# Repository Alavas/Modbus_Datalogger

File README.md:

# Modbus_Datalogger

Web based data logger.

This device can communicate with any of the Grundfos E-Products through a ModBus interface. Currently it the programming is optimized to work with the Magna3 product line. The Parallax Propeller receives the ModBus data over RS485 and then does the decoding and unit conversion of the pump data. The Electric Imp (SD card shape) polls the Propeller for the new data and then adds its own data. The Electric Imp currently has 3 external thermistors as well as its on board light sensor. This data is packaged on the device and send on to the Electric Imp agent(https://electricimp.com/docs/api/agent/). The Imp agent then breaks up the data and sends the requested data to the Phant(http://phant.io/about/) data server. The server exists currently on a Amazon Web Services EC2 Micro Instance Linux server. In order to view the data a web page interface is used. This web page uses Google Charts to display data from the Phant server. Additional static information is displayed at the bottom of the web page, this information is grabbed from the Electric Imp agent.

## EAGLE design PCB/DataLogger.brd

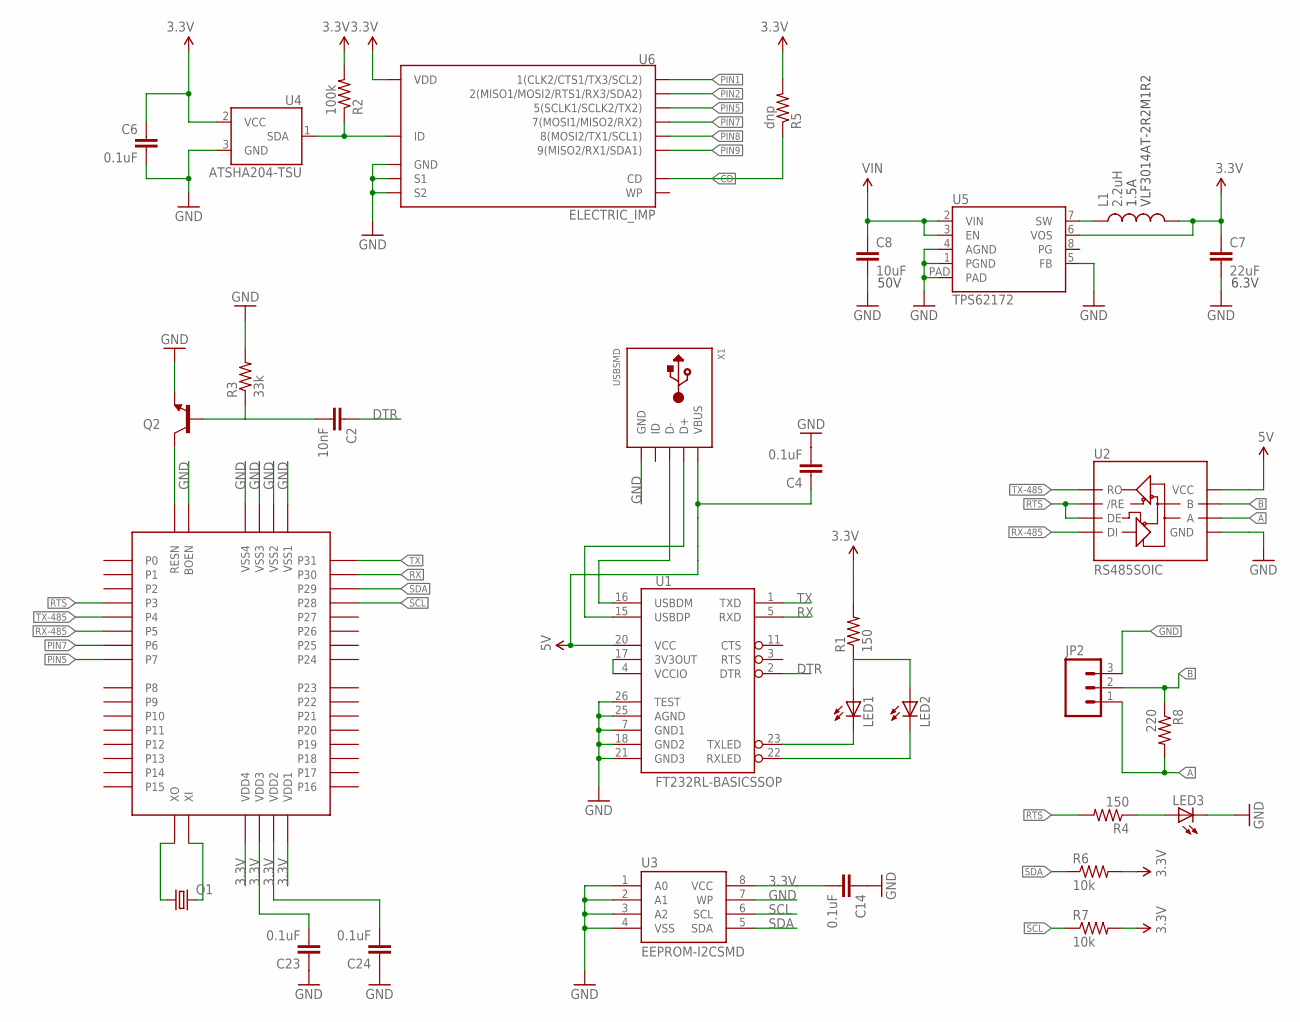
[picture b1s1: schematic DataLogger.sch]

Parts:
C2: 10nF; 0805
C4: 0.1uF; 1210
C6: 0.1uF; 0603-CAP
C7: 22uF; 0805
C8: 10uF; 1210
C14, C23, C24: 0.1uF; 0805
JP2: M03PTH; 1X03
L1: 2.2uH; VLF4012A
LED1, LED2, LED3: LED1206; LED-1206
Q1: CRYSTALSM49; SM49
Q2: TRANSISTOR_NPNSOT23; SOT23
R1, R4: 150; 0805
R2: 100k; 0603-RES
R3: 33k; 0805
R5: dnp; 0603-RES
R6, R7: 10k; 0805
R8: 220; 0805
U1: FT232RL-BASICSSOP; SSOP28DB
U2: RS485SOIC; SO08
U3: EEPROM-I2CSMD; SO08
U4: ATSHA204-TSU; SOT23-3
U5: TPS62172; WSON-8-PAD
U6: ELECTRIC_IMP; SD_1:1
U7: PROPELLERSURFACELQFP; SURFACEMOUNT
X1: USBSMD; USB-MINIB

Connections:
3.3V: C6.1, C7.1, C14.2, C23.2, C24.2, L1.P$2 (2), R1.2, R2.2, R5.2, R6.2, R7.2, U3.8 (VCC), U4.2 (VCC), U5.6 (VOS), U6.4 (VDD), U7.8 (VDD1), U7.18 (VDD2), U7.30 (VDD3), U7.40 (VDD4)
5V: C4.1, C8.1, U1.20 (VCC), U2.8 (VCC), U5.2 (VIN), U5.3 (EN), X1.VBUS
A: JP2.1, R8.2, U2.6 (A)
B: JP2.2, R8.1, U2.7 (B)
CD: R5.1, U6.CD
DTR: C2.1, C2.2, Q2.1 (B), R3.1, U1.2 (DTR)
GND: C4.2, C6.2, C7.2, C8.2, C14.1, C23.1, C24.1, JP2.3, LED3.C, Q2.2 (E), R3.2, U1.7 (GND1), U1.18 (GND2), U1.21 (GND3), U1.25 (AGND), U1.26 (TEST), U2.5 (GND), U3.1 (A0), U3.2 (A1), U3.3 (A2), U3.4 (VSS), U3.7 (WP), U4.3 (GND), U5.1 (PGND), U5.4 (AGND), U5.5 (FB), U5.PAD, U6.3 (GND), U6.SH@1 (S1), U6.SH@2 (S2), U7.5 (VSS1), U7.6 (BOEN), U7.17 (VSS2), U7.27 (VSS3), U7.39 (VSS4), X1.GND
ID: R2.1, U4.1 (SDA), U6.6 (ID)
unnamed: U1.16 (USBDM), X1.D-
unnamed: U1.15 (USBDP), X1.D+
unnamed: Q2.3 (C), U7.7 (RESN)
unnamed: U1.4 (VCCIO), U1.17 (3V3OUT)
unnamed: Q1.2, U7.28 (XI)
unnamed: Q1.1, U7.29 (XO)
unnamed: L1.P$1 (1), U5.7 (SW)
unnamed: LED1.C, U1.23 (TXLED)
unnamed: LED2.C, U1.22 (RXLED)
unnamed: LED1.A, LED2.A, R1.1
unnamed: LED3.A, R4.1
PIN1: U6.1 (1(CLK2/CTS1/TX3/SCL2))
PIN2: U6.2 (2(MISO1/MOSI2/RTS1/RX3/SDA2))
PIN5: U6.5 (5(SCLK1/SCLK2/TX2)), U7.4 (P7)
PIN7: U6.7 (7(MOSI1/MISO2/RX2)), U7.3 (P6)
PIN8: U6.8 (8(MOSI2/TX1/SCL1))
PIN9: U6.9 (9(MISO2/RX1/SDA1))
RTS: R4.2, U2.2 (/RE), U2.3 (DE), U7.44 (P3)
RX: U1.5 (RXD), U7.37 (P30)
RX-485: U2.4 (DI), U7.2 (P5)
SCL: R7.1, U3.6 (SCL), U7.35 (P28)
SDA: R6.1, U3.5 (SDA), U7.36 (P29)
TX: U1.1 (TXD), U7.38 (P31)
TX-485: U2.1 (RO), U7.1 (P4)

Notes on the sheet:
50V
6.3V
1.5A
VLF3014AT-2R2M1R2

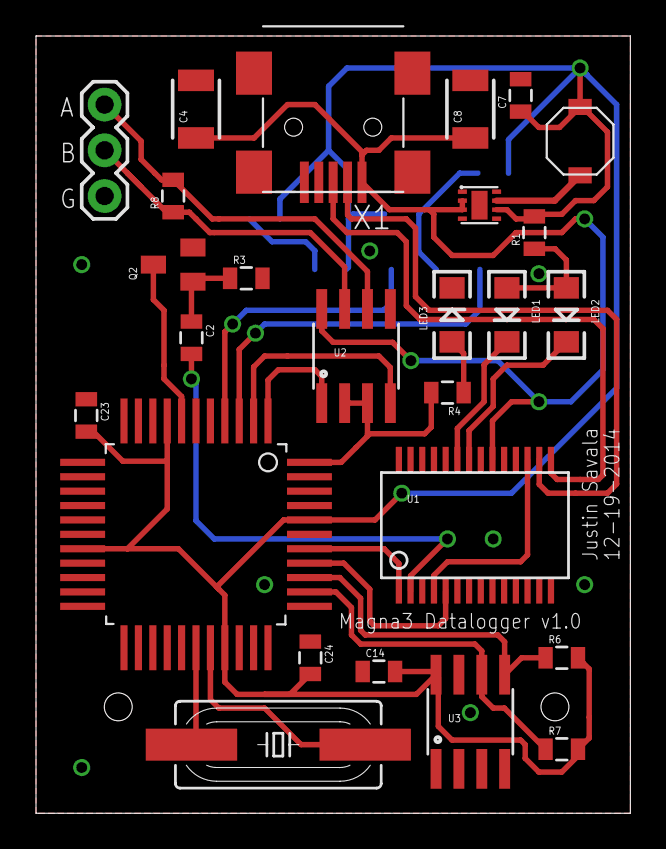
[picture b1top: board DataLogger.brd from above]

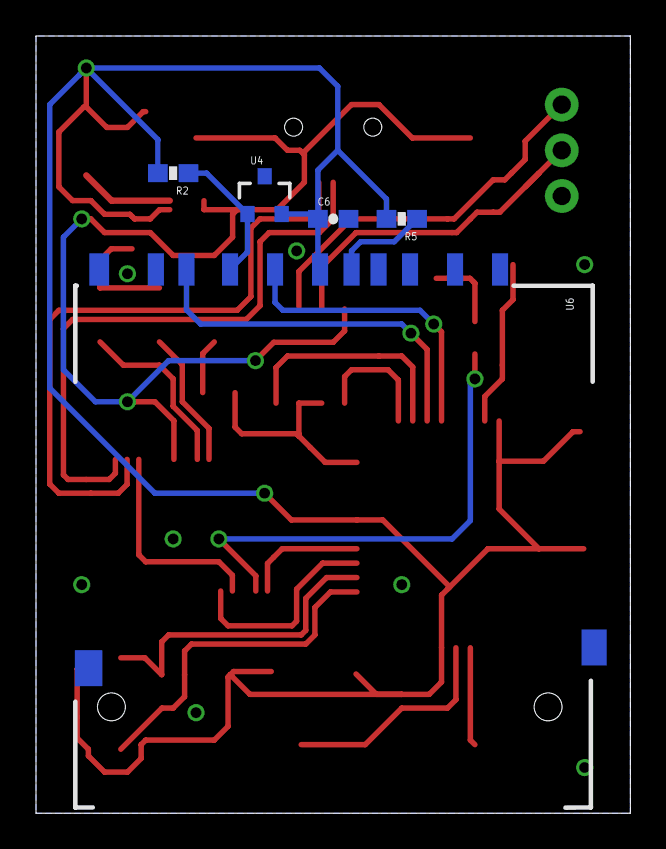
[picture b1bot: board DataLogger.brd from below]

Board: 2 copper layers, 33.0 x 43.2 mm, 31 parts (5 on the bottom side), 28 nets.

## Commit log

2015-01-27 Initial
2015-01-28 Added files.
2015-01-28 Reorganized
2015-01-28 Added Propeller Program files.
2015-01-29 Added file.
2015-01-30 Worked on programs.
2015-02-14 Updated files.
2015-02-15 Removed/Edited files.
2015-02-20 Updated programs.
2015-02-23 Added enclosure drawings.
2015-02-24 Added image.
2015-02-24 Added Electric Imp files.
2015-02-24 Added PCB files.
2015-02-24 Added web page.
2015-02-24 Added photos.
2015-02-24 Updated readme.
2016-12-18 Modded
2016-12-18 Changed README file.

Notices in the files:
parts and their libraries:
SparkFun-DigitalIC: Licensing: CC v3.0 Share-Alike You are welcome to use this library for commercial purposes.
SparkFun-Resistors: Licensing: Creative Commons ShareAlike 4.0 International - https://creativecommons.org/licenses/by-sa/4.0
